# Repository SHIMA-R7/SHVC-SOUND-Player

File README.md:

# SHVC-SOUND スタンドアロンプレイヤー

## ESP32 r0.4基板を使う場合

PCからSPCファイルを再生するESP32用ファームは
`SHVC-SOUND_python/esp32_spc_uploader/`。
準備・書き込み・IPL診断・テスト音の順序は
[ESP32 SPC立ち上げ手順](docs/esp32-spc-bringup.md)を参照。
2026-10-04にSPC全体転送3回連続成功、タイトル曲とWAV由来の短い音声の可聴再生を確認。
WAV一括再生は`SHVC-SOUND_python/tools/wav_clip_esp32.py`を使用する。
[実機確認結果・WAVの使い方・アンプのバイパス](docs/esp32-playback-results.md)も参照。
PCを使わず電源投入から再生する場合は、[単体再生ファーム](docs/esp32-standalone.md)を使用する。
BluetoothでSPC・MIDI・短いWAVを保存・再生し、MIDI演奏や音量・パン・音色を操作する場合は、
[Bluetooth PlayerとWindows操作画面](docs/esp32-bluetooth.md)を使用する。
既存の`esp32_ble_midi/`はBLE／USB MIDI演奏用の別ファーム。
以下のArduino配線と自己診断スケッチはUno／Nano用。

Arduino Uno R3 / Nano (ATmega328P・5Vロジック) で SHVC-SOUND(スーファミ音源モジュール: S-SMP + S-DSP + ARAM + DAC)を駆動し、
`.spc` ファイルを実チップで再生するプロジェクト。音声は TDA7053A(ステレオBTL)で増幅し3.5mmジャックへ出力する。

## 構成

| ディレクトリ | 内容 |
|---|---|
| `SHVC-SOUND-KiCad_project/` | 基板設計(KiCad)。スキーマ・PCB・カスタムフットプリント |
| `SHVC-SOUND_python/` | 再生ソフト一式 |
| `SHVC-SOUND_python/spc_gui.py` | **GUIアプリ**(Tkinter製)。プレイリスト再生・音量調整・ROM解析 |
| `SHVC-SOUND_python/spc_play.py` | PC側。`.spc` を解析しシリアル経由でArduinoへ転送する(CLI/GUI共用) |
| `SHVC-SOUND_python/rom_tools.py` | スーファミROMの内部ヘッダ解析(マッパ判別・チェックサム検証) |
| `SHVC-SOUND_python/spc_uploader/` | Arduino側。シリアルコマンドをSPC700 IPL ROMプロトコルへ変換する |
| `SHVC-SOUND_python/hw_selftest/` | Arduino単体で動く自己診断。PCなしでノイズを鳴らして配線を検証する |
| `docs/minimal-bringup.md` | 最小構成での実機立ち上げ手順と配線表 |

## まず実機で音を確認する

いきなり `spc_play.py` を試す前に、アンプと12V系を外した最小構成で
`hw_selftest/hw_selftest.ino` を走らせる。ハードの問題か転送ソフトの問題かが一発で切り分けられる。
手順と配線表は [docs/minimal-bringup.md](docs/minimal-bringup.md) を参照。

## GUIアプリ

```bash
python spc_gui.py
```

- プレイリストに `.spc` をまとめて登録して再生。ID666タグ(曲名・ゲーム・作曲者)を表示
- DSP音量倍率とアンプPWM音量をスライダーで調整
- 転送はワーカースレッドで実行され、進捗バーとログをリアルタイム表示。中止も可能
- **フォルダ監視**: エミュレータのSPC出力先を指定しておくと、新しくダンプされた
  `.spc` を自動でプレイリストに追加する
- ROM解析タブ: 吸い出したROMのタイトル・マッパ(LoROM/HiROM/ExHiROM)・容量・
  リージョン・チェックサムを表示

### ROMからのSPC抽出について

**ROMの中に `.spc` は入っていない**ため、直接抽出はできない。
`.spc` はSPC700が曲を再生中の ARAM 64KB + DSPレジスタ + CPUレジスタの
スナップショットであり、ROMにあるのはサウンドドライバ・BRRサンプル・
シーケンスデータがバラバラに格納されたもの。ARAMの完成イメージは
ゲームを実際に起動して初めて組み上がる。

実用的な手順は、SPCダンプ機能を持つエミュレータ(Mesen2、bsnes/higan、
一部のSnes9xビルド)でROMを動かし、曲の再生中にダンプすること。
出力先をGUIの「フォルダを監視」に指定しておけば、ダンプした瞬間に
プレイリストへ入って実機で鳴らせる。

## CLIでの使い方

Arduino IDE で `spc_uploader/spc_uploader.ino` を書き込み、以下を実行する。

```bash
python spc_play.py COM3 song.spc
```

`pyserial` が必要:

```bash
pip install pyserial
```

診断用フラグ: `--test`(強制ノイズ再生)、`--skip-bulk`、`--low-addr`、`--only-stub`

## 配線 (Arduino ⇔ SHVC-SOUND 24pin)

| Arduino | SHVC-SOUND pin | 信号 |
|---|---|---|
| D2-D9 | 7-14 | D0-D7 |
| A0 | 3 | A0 |
| A1 | 4 | A1 |
| A2 | 5 | /WR |
| A3 | 6 | /RD |
| A4 | 15 | /RESET |
| D10 | 20 | /MUTE(常時HIGH固定) |
| - | 2 / 1 | CS→+5V / /CS→GND 直結 |
| - | 18, 24 | VCC, VS → +5V |
| - | 19, 23 | GND |
| - | 21, 22 | Audio-L / Audio-R → アンプ入力 |

ロジック系(5V)とアンプ系(12V)は別電源。Arduinoのレギュレータからアンプ用12Vを取らないこと。

## 既知の問題

- **復元スタブが曲データを上書きする**: `spc_play.py` のDSP復元スタブは約800バイトあり `$FFC0` 直下(≒`$FC9B`)に配置されるが、
  この領域はメインRAM転送範囲(`$0100-$FFBF`)と重なるため曲データを約800バイト破壊する。
  この領域をサンプルやエコーバッファに使う曲ではノイズが出る。エコーバッファ領域への配置か、スタブのループ化による小型化が要検討。
- **基板のDRC違反が未修正**: シルク重なり2件、シルクが銅箔にかかる6件、フットプリント型不一致1件、ライブラリ不一致1件。
- 実機での動作確認は未完了。
- **基板のSHVC-SOUNDフットプリントに1番ピンの表示が無い**: `SHVC-SOUND-MB.kicad_mod` は
  パッド24個すべてが丸、シルクにピン番号も1番マーカーも無い(リファレンス指定子のみ)。
  コネクタ自体にキーが無く逆挿しできてしまうため、シルクに `1` の印字と極性マークを追加すべき。
- **基板はArduino Nanoフットプリント**(`Module:Arduino_Nano_WithMountingHoles`)。
  Uno R3はピン互換だがフットプリントが合わないため、基板に載せる場合は要変更。ジャンパ配線での検証には支障なし。

## ライセンス / 帰属

基板設計の一部は [OpenSFC](https://github.com/starlightk7/OpenSFC)(© 2025 starlightk7、CERN-OHL-S)に由来する。
詳細と再頒布時の義務は `SHVC-SOUND-KiCad_project/SHVC-SOUND-KiCad/THIRD_PARTY_NOTICE_OpenSFC.txt` を参照。
公開・頒布する場合は CERN-OHL-S 3.3 に従い、改変内容の要約を同NOTICEに追記すること。

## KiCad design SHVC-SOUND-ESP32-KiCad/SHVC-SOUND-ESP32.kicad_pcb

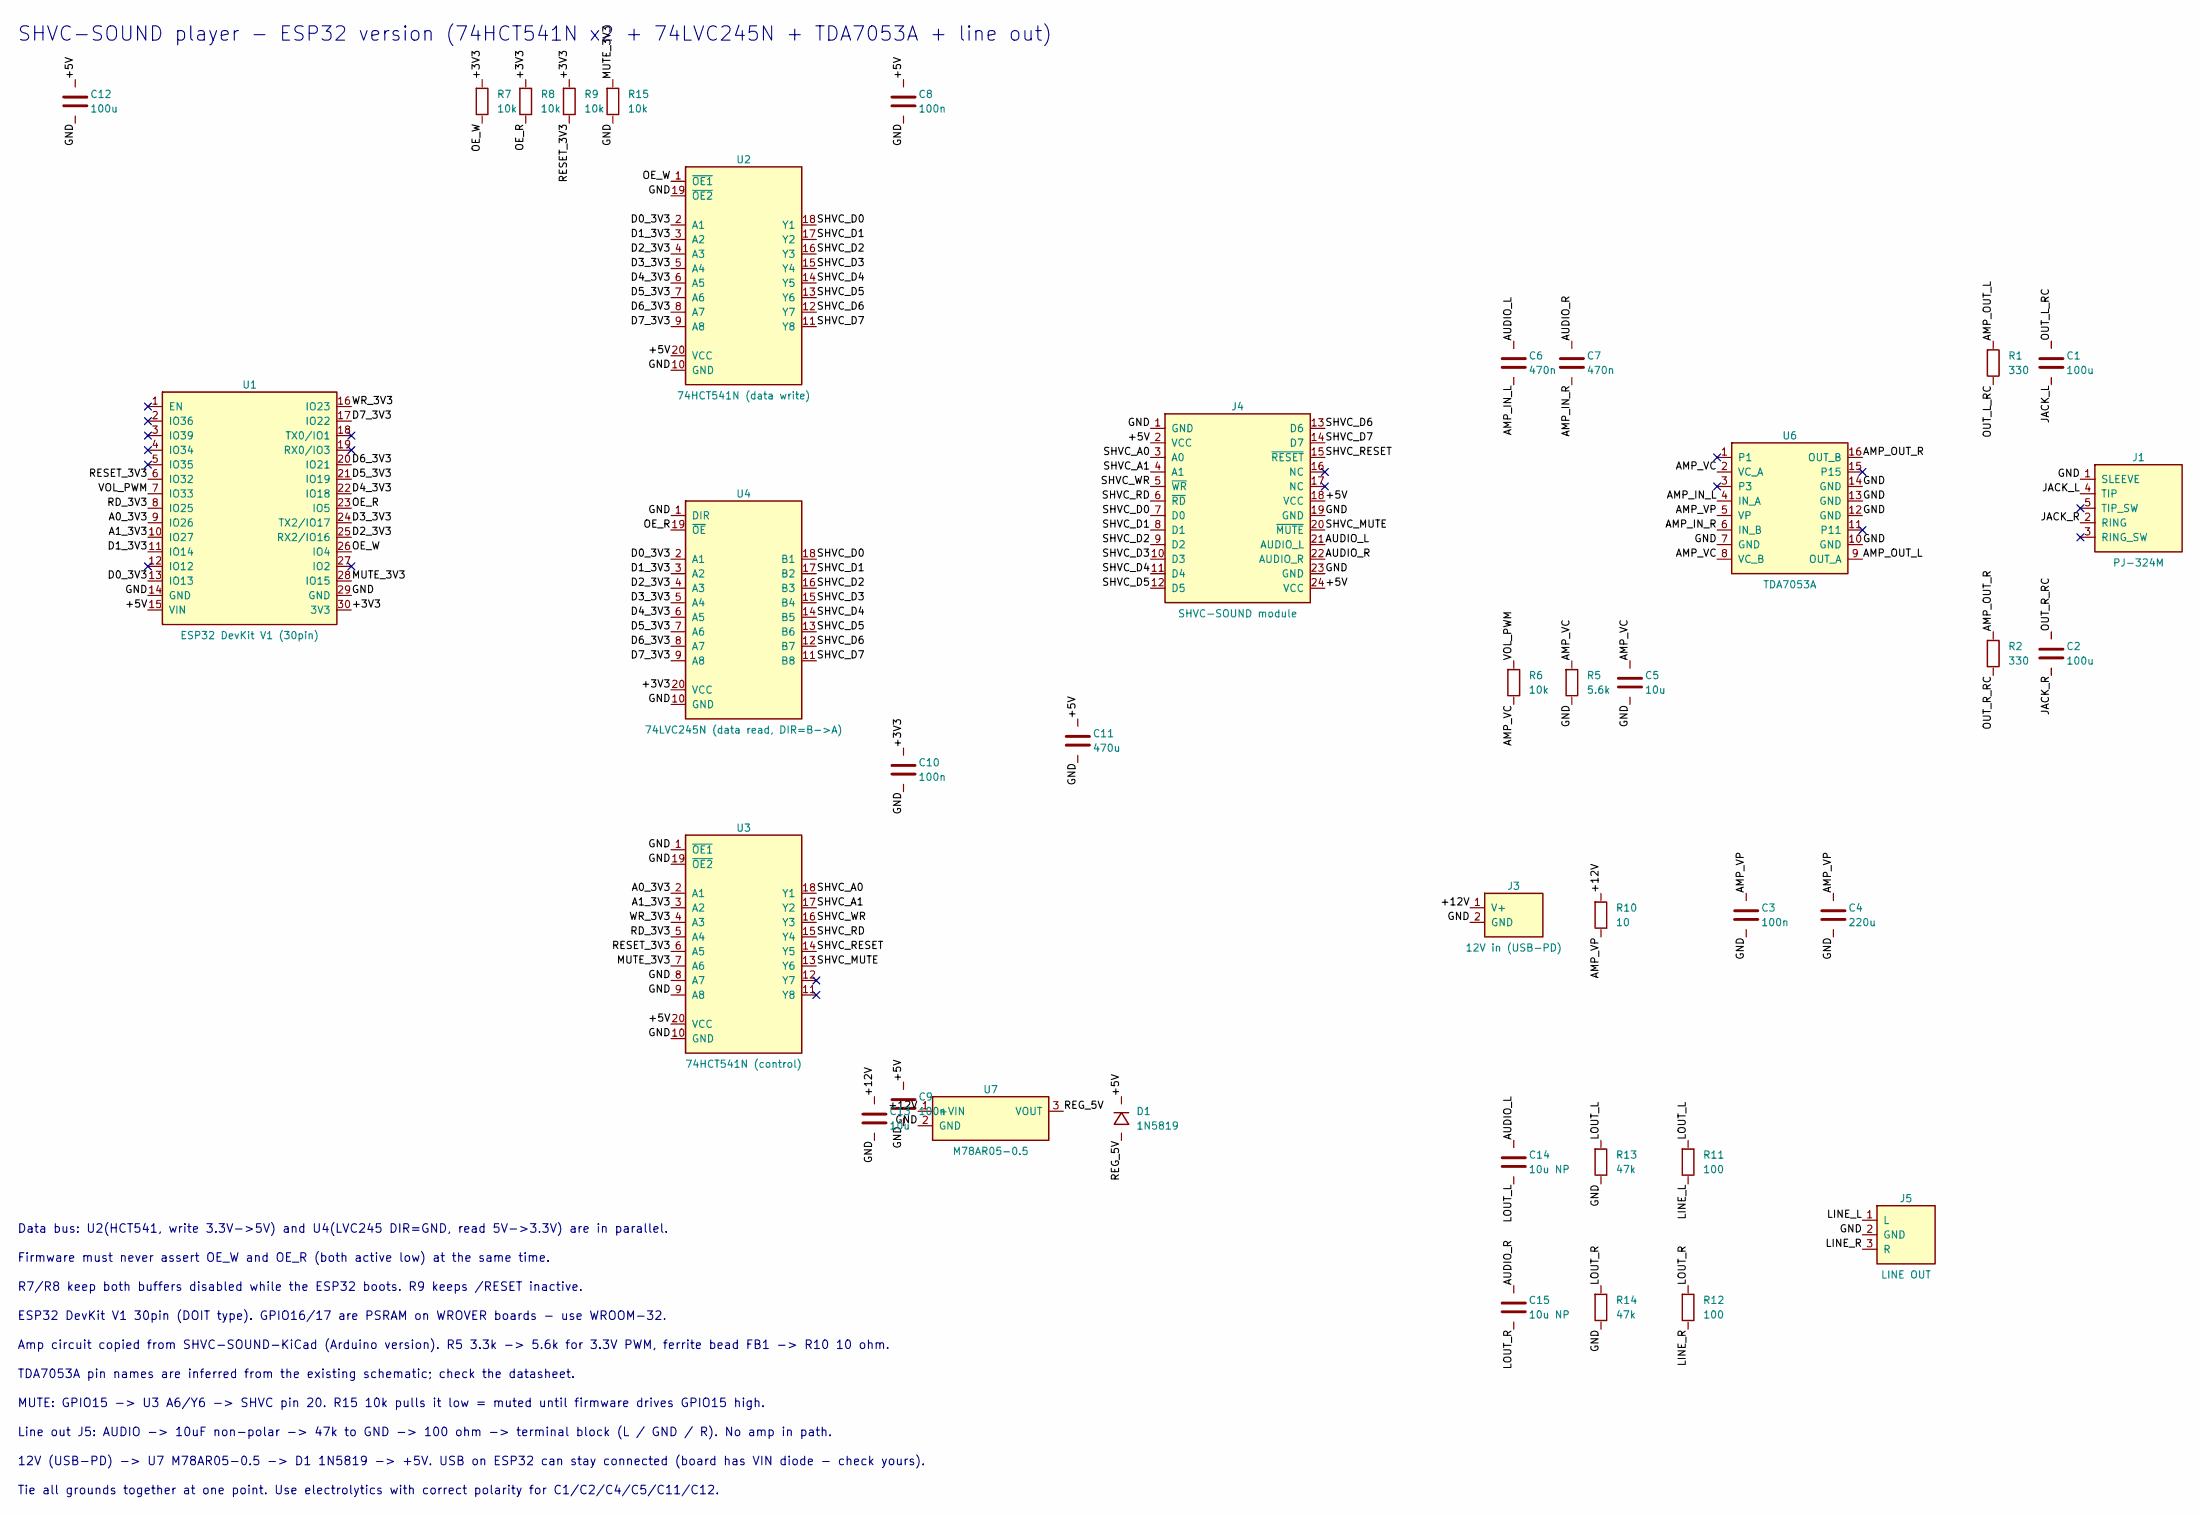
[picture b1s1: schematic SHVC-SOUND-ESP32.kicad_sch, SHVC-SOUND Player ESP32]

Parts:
C1, C2, C12: 100u; CP_Radial_D6.3mm_P2.50mm
C3, C8, C9, C10: 100n; C_Disc_D3.0mm_W1.6mm_P2.50mm
C4: 220u; CP_Radial_D8.0mm_P3.50mm
C5, C13: 10u; CP_Radial_D5.0mm_P2.00mm
C6, C7: 470n; C_Disc_D5.0mm_W2.5mm_P5.00mm
C11: 470u; CP_Radial_D10.0mm_P5.00mm
C14, C15: 10u NP; CP_Radial_D4.0mm_P1.50mm
D1: 1N5819; D_DO-41_SOD81_P7.62mm_Horizontal
J1: PJ-324M
J3: 12V in (USB-PD); PD_INPUT_MODULE_2P
J4: SHVC-SOUND module; SHVC-SOUND-MB
J5: LINE OUT; TerminalBlock_Phoenix_PT-1,5-3-3.5-H_1x03_P3.50mm_Horizontal
R1, R2: 330; R_Axial_DIN0207_L6.3mm_D2.5mm_P7.62mm_Horizontal
R5: 5.6k; R_Axial_DIN0207_L6.3mm_D2.5mm_P7.62mm_Horizontal
R6, R7, R8, R9: 10k; R_Axial_DIN0207_L6.3mm_D2.5mm_P7.62mm_Horizontal
R10: 10; R_Axial_DIN0207_L6.3mm_D2.5mm_P7.62mm_Horizontal
R11, R12: 100; R_Axial_DIN0207_L6.3mm_D2.5mm_P2.54mm_Vertical
R13, R14: 47k; R_Axial_DIN0207_L6.3mm_D2.5mm_P2.54mm_Vertical
R15: 10k; R_Axial_DIN0207_L6.3mm_D2.5mm_P2.54mm_Vertical
U1: ESP32 DevKit V1 (30pin); ESP32-DevKit-30_Socket
U2: 74HCT541N (data write); DIP-20_W7.62mm
U3: 74HCT541N (control); DIP-20_W7.62mm
U4: 74LVC245N (data read, DIR=B->A); DIP-20_W7.62mm
U6: TDA7053A; DIP-16_W7.62mm
U7: M78AR05-0.5; DCDC_SIP3_7805

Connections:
+3V3: C10.1 (K), R7.1 (K), R8.1 (K), R9.1 (K), U1.30 (3V3), U4.20 (VCC)
+5V: C8.1 (K), C9.1 (K), C11.1 (K), C12.1 (K), D1.1 (K), J4.2 (VCC), J4.18 (VCC), J4.24 (VCC), U1.15 (VIN), U2.20 (VCC), U3.20 (VCC)
+12V: C13.1 (K), J3.1 (V+), R10.1 (K), U7.1 (+VIN)
A0_3V3: U1.9 (IO26), U3.2 (A1)
A1_3V3: U1.10 (IO27), U3.3 (A2)
AMP_IN_L: C6.2 (A), U6.4 (IN_A)
AMP_IN_R: C7.2 (A), U6.6 (IN_B)
AMP_OUT_L: R1.1 (K), U6.9 (OUT_A)
AMP_OUT_R: R2.1 (K), U6.16 (OUT_B)
AMP_VC: C5.1 (K), R5.1 (K), R6.2 (A), U6.2 (VC_A), U6.8 (VC_B)
AMP_VP: C3.1 (K), C4.1 (K), R10.2 (A), U6.5 (VP)
AUDIO_L: C6.1 (K), C14.1 (K), J4.21 (AUDIO_L)
AUDIO_R: C7.1 (K), C15.1 (K), J4.22 (AUDIO_R)
D0_3V3: U1.13 (IO13), U2.2 (A1), U4.2 (A1)
D1_3V3: U1.11 (IO14), U2.3 (A2), U4.3 (A2)
D2_3V3: U1.25 (RX2/IO16), U2.4 (A3), U4.4 (A3)
D3_3V3: U1.24 (TX2/IO17), U2.5 (A4), U4.5 (A4)
D4_3V3: U1.22 (IO18), U2.6 (A5), U4.6 (A5)
D5_3V3: U1.21 (IO19), U2.7 (A6), U4.7 (A6)
D6_3V3: U1.20 (IO21), U2.8 (A7), U4.8 (A7)
D7_3V3: U1.17 (IO22), U2.9 (A8), U4.9 (A8)
GND: C3.2 (A), C4.2 (A), C5.2 (A), C8.2 (A), C9.2 (A), C10.2 (A), C11.2 (A), C12.2 (A), C13.2 (A), J1.1 (SLEEVE), J3.2 (GND), J4.1 (GND), J4.19 (GND), J4.23 (GND), J5.2 (GND), R5.2 (A), R13.2 (A), R14.2 (A), R15.2 (A), U1.14 (GND), U1.29 (GND), U2.10 (GND), U2.19 (~OE2), U3.1 (~OE1), U3.8 (A7), U3.9 (A8), U3.10 (GND), U3.19 (~OE2), U4.1 (DIR), U4.10 (GND), U6.7 (GND), U6.10 (GND), U6.12 (GND), U6.13 (GND), U6.14 (GND), U7.2 (GND)
JACK_L: C1.2 (A), J1.4 (TIP)
JACK_R: C2.2 (A), J1.2 (RING)
LINE_L: J5.1 (L), R11.2 (A)
LINE_R: J5.3 (R), R12.2 (A)
LOUT_L: C14.2 (A), R11.1 (K), R13.1 (K)
LOUT_R: C15.2 (A), R12.1 (K), R14.1 (K)
MUTE_3V3: R15.1 (K), U1.28 (IO15), U3.7 (A6)
OE_R: R8.2 (A), U1.23 (IO5), U4.19 (~OE)
OE_W: R7.2 (A), U1.26 (IO4), U2.1 (~OE1)
OUT_L_RC: C1.1 (K), R1.2 (A)
OUT_R_RC: C2.1 (K), R2.2 (A)
RD_3V3: U1.8 (IO25), U3.5 (A4)
REG_5V: D1.2 (A), U7.3 (VOUT)
RESET_3V3: R9.2 (A), U1.6 (IO32), U3.6 (A5)
SHVC_A0: J4.3 (A0), U3.18 (Y1)
SHVC_A1: J4.4 (A1), U3.17 (Y2)
SHVC_D0: J4.7 (D0), U2.18 (Y1), U4.18 (B1)
SHVC_D1: J4.8 (D1), U2.17 (Y2), U4.17 (B2)
SHVC_D2: J4.9 (D2), U2.16 (Y3), U4.16 (B3)
SHVC_D3: J4.10 (D3), U2.15 (Y4), U4.15 (B4)
SHVC_D4: J4.11 (D4), U2.14 (Y5), U4.14 (B5)
SHVC_D5: J4.12 (D5), U2.13 (Y6), U4.13 (B6)
SHVC_D6: J4.13 (D6), U2.12 (Y7), U4.12 (B7)
SHVC_D7: J4.14 (D7), U2.11 (Y8), U4.11 (B8)
SHVC_MUTE: J4.20 (~MUTE), U3.13 (Y6)
SHVC_RD: J4.6 (~RD), U3.15 (Y4)
SHVC_RESET: J4.15 (~RESET), U3.14 (Y5)
SHVC_WR: J4.5 (~WR), U3.16 (Y3)
VOL_PWM: R6.1 (K), U1.7 (IO33)
WR_3V3: U1.16 (IO23), U3.4 (A3)

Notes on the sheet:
SHVC-SOUND player - ESP32 version (74HCT541N x2 + 74LVC245N + TDA7053A + line out)
Data bus: U2(HCT541, write 3.3V->5V) and U4(LVC245 DIR=GND, read 5V->3.3V) are in parallel.
Firmware must never assert OE_W and OE_R (both active low) at the same time.
R7/R8 keep both buffers disabled while the ESP32 boots. R9 keeps /RESET inactive.
ESP32 DevKit V1 30pin (DOIT type). GPIO16/17 are PSRAM on WROVER boards - use WROOM-32.
Amp circuit copied from SHVC-SOUND-KiCad (Arduino version). R5 3.3k -> 5.6k for 3.3V PWM, ferrite bead FB1 -> R10 10 ohm.
TDA7053A pin names are inferred from the existing schematic; check the datasheet.
MUTE: GPIO15 -> U3 A6/Y6 -> SHVC pin 20. R15 10k pulls it low = muted until firmware drives GPIO15 high.
Line out J5: AUDIO -> 10uF non-polar -> 47k to GND -> 100 ohm -> terminal block (L / GND / R). No amp in path.
12V (USB-PD) -> U7 M78AR05-0.5 -> D1 1N5819 -> +5V. USB on ESP32 can stay connected (board has VIN diode - check yours).
Tie all grounds together at one point. Use electrolytics with correct polarity for C1/C2/C4/C5/C11/C12.

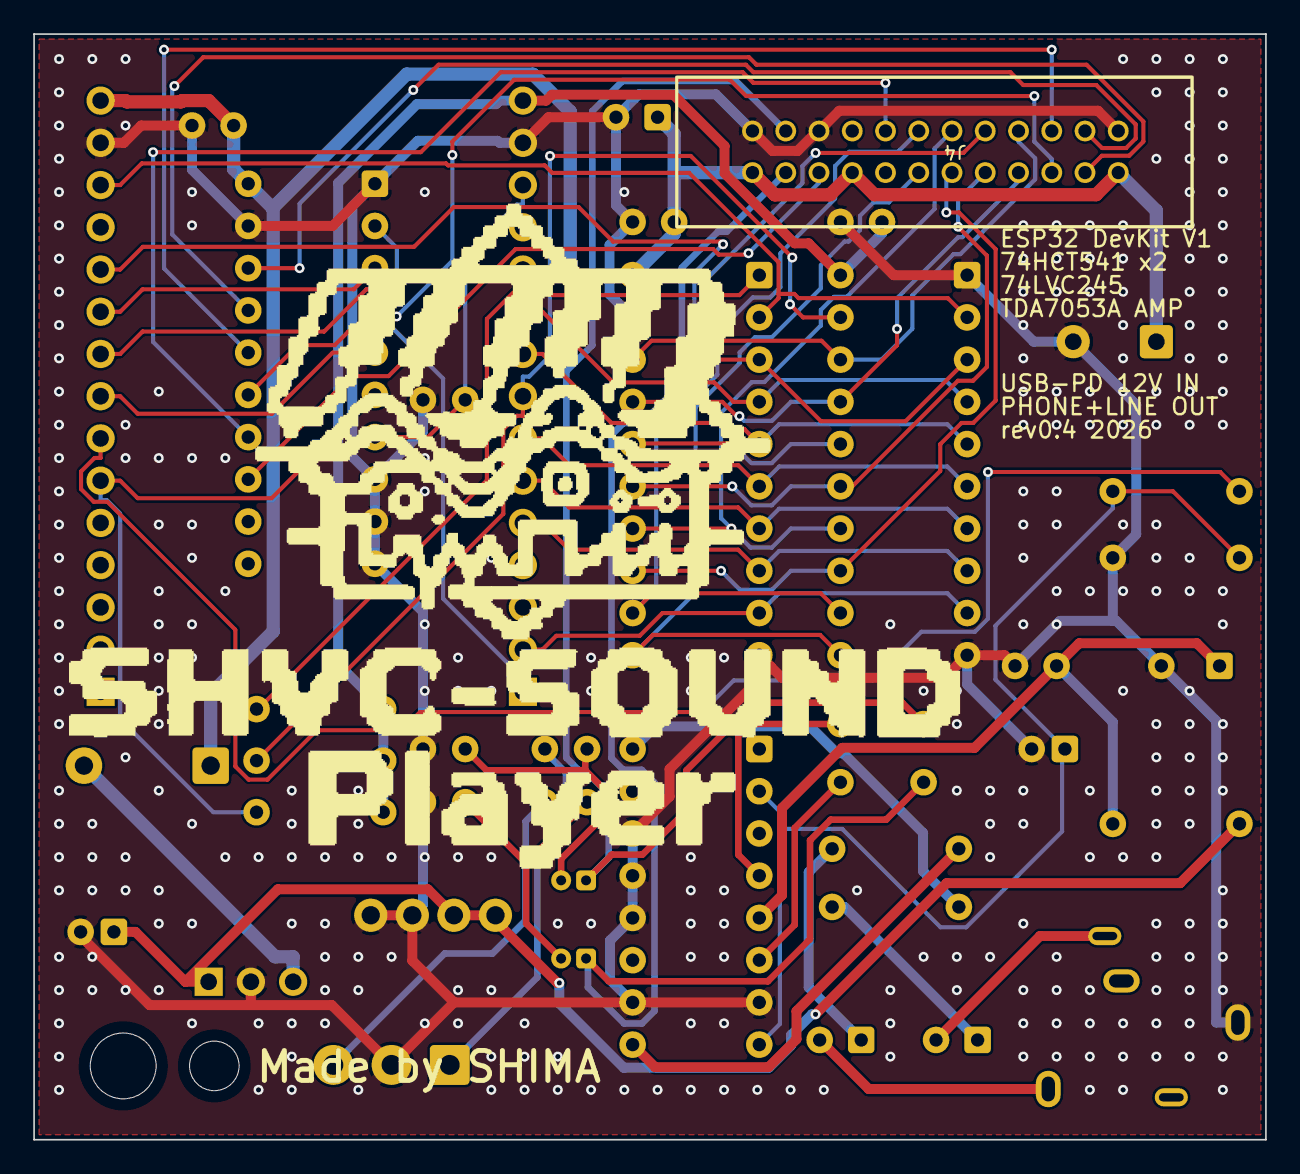
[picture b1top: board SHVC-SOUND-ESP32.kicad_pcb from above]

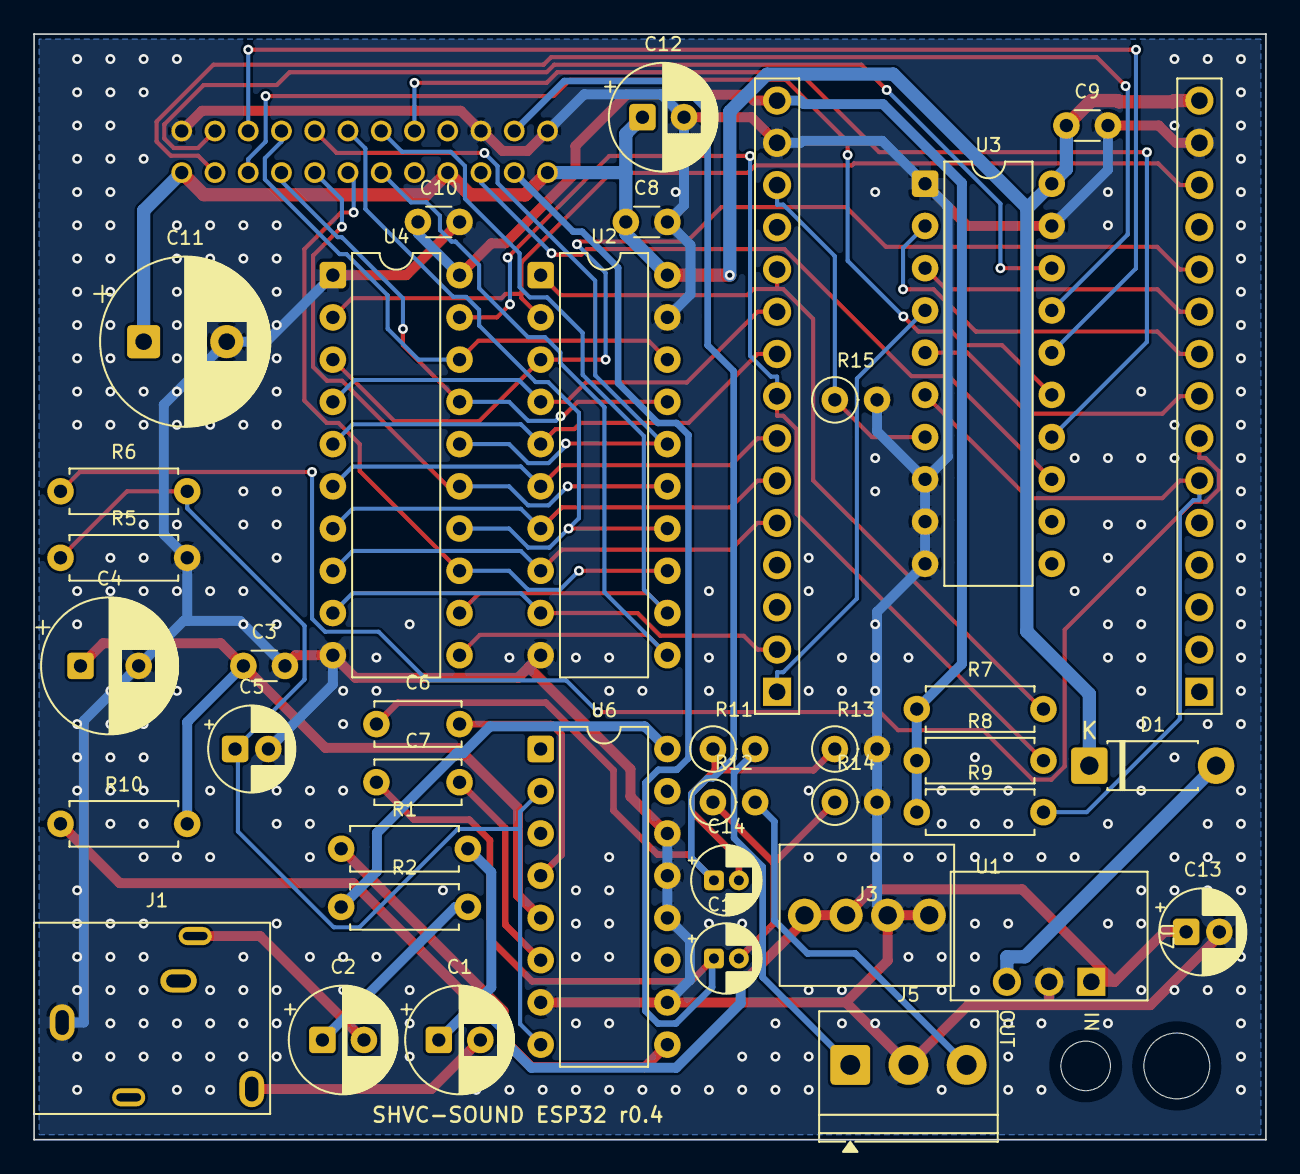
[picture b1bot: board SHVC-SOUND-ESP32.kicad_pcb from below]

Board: 2 copper layers, 74.1 x 66.5 mm, 41 parts (38 on the bottom side), 52 nets.

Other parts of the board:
H1: hole 3.96mm; NPTH_Hole_3.96mm
H2: hole 2.98mm; NPTH_Hole_2.98mm

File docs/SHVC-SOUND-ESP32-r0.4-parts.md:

# SHVC-SOUND-ESP32 rev0.4 部品表

対象：ESP32版 rev0.4（74.09 × 66.5mm）。2026-10-02時点。現行BOMから自動生成し、PCBの部品番号を照合。**実機動作は未検証**。

Arduino Nano版の部品表ではありません。SHVC-SOUND音源モジュール本体、12V対応USB-PD電源・ケーブルは別途用意してください。

## 1. IC・モジュール・電源

| 部品番号 | 数量 | 品名・値 | 仕様・取り付け上の注意 |
| --- | --- | --- | --- |
| U2 | 1 | 74HCT541N | DIP-20。データ書き込み(3.3V→5V)。ICソケット可 |
| U3 | 1 | 74HCT541N | DIP-20。制御線(3.3V→5V)。ESP32の下なのでソケット不可・直付け |
| U4 | 1 | 74LVC245N | DIP-20。データ読み出し(5V→3.3V)。ICソケット可 |
| U6 | 1 | TDA7053A | DIP-16。ステレオアンプ。ICソケット可 |
| U1 | 1 | ESP32 DevKit V1 | 30ピン(DOIT互換) 列間25.4mm。WROOM-32搭載品 |
| J3 | 1 | USB-PDトリガーモジュール(12V) | 既存基板と同じPD_INPUT_MODULE。全体の電源入力(12V) |
| U7 | 1 | M78AR05-0.5(MINMAX) | 12V→5V 0.5A DC-DCコンバータ 7805互換SIP3。既存Arduino版と同じ部品 |
| D1 | 1 | 1N5819 | ショットキーダイオード 1A DO-41 リード間7.62mm。DC-DC出力→+5V(USB給電との逆流防止) |

## 2. 抵抗

| 部品番号 | 数量 | 品名・値 | 仕様・取り付け上の注意 |
| --- | --- | --- | --- |
| R1 R2 | 2 | 330Ω | 1/4W 炭素皮膜 リード間7.62mm。ヘッドホン出力直列 |
| R5 | 1 | 5.6kΩ | 1/4W 炭素皮膜 リード間7.62mm。音量電圧の分圧(3.3V PWM用) |
| R10 | 1 | 10Ω | 1/4W 炭素皮膜 リード間7.62mm。12V入力のノイズ除去(C4と約72Hzのローパス) |
| R6 R7 R8 R9 | 4 | 10kΩ | 1/4W 炭素皮膜 リード間7.62mm。R6=音量PWM R7/R8=OEプルアップ R9=/RESETプルアップ |
| R11 R12 | 2 | 100Ω | 1/4W 炭素皮膜 立て付け(リード間2.54mm)。ライン出力の保護(ESP32の下なので高さ10mm以下に) |
| R13 R14 | 2 | 47kΩ | 1/4W 炭素皮膜 立て付け(リード間2.54mm)。ライン出力を0V基準に固定(抜き差し時のポップ防止) |
| R15 | 1 | 10kΩ | 1/4W 炭素皮膜 立て付け(リード間2.54mm)。MUTE引き下げ(ESP32起動中は消音) |

## 3. コンデンサ

| 部品番号 | 数量 | 品名・値 | 仕様・取り付け上の注意 |
| --- | --- | --- | --- |
| C3 C8 C9 C10 | 4 | 100nF | 積層セラミック 50V リード間2.5mm。パスコン |
| C6 C7 | 2 | 470nF | 積層セラミックまたはフィルム 50V リード間5.0mm。音声入力の直流カット |
| C5 | 1 | 10µF | 電解 16V以上 φ5mm リード間2.0mm。音量電圧の平滑 |
| C13 | 1 | 10µF | 電解 25V以上 φ5mm リード間2.0mm。DC-DC入力(12V) |
| C14 C15 | 2 | 10µF 無極性(バイポーラ) | 電解 16V以上 φ4mm リード間1.5mm。ライン出力の直流カット(向きなし) |
| C1 C2 | 2 | 100µF | 電解 16V以上 φ6.3mm リード間2.5mm。ヘッドホン出力の直流カット |
| C12 | 1 | 100µF | 電解 10V以上 φ6.3mm リード間2.5mm。ESP32側5V |
| C4 | 1 | 220µF | 電解 25V以上 φ8mm リード間3.5mm。12V平滑 |
| C11 | 1 | 470µF | 電解 10V以上 φ10mm リード間5.0mm。SHVC-SOUND側5V |

## 4. コネクタ・ソケット・基板

| 部品番号 | 数量 | 品名・値 | 仕様・取り付け上の注意 |
| --- | --- | --- | --- |
| J1 | 1 | PJ-324M | 3.5mmステレオジャック 5ピン(SOFNG LCSC C22355739)。1=GND 4=L 2=R(推定・要導通確認) |
| J5 | 1 | ターミナルブロック 3P | 3.5mmピッチ 横入れ(Phoenix PT-1.5-3-3.5-H 相当)。ライン出力 L/GND/R(アンプを通さない) |
| J4用 | 2 | ピンソケット 1x12 | 2.0mmピッチ 1列 12ピン。2本を列間2.5mmで並べてSHVC-SOUNDを受ける |
| U1用 | 2 | ピンソケット 1x15 | 2.54mmピッチ 1列 15ピン 高さ8.5mm前後。ESP32を挿す |
| - | 1 | SHVC-SOUND-ESP32 r0.4 | 2層 74.09×66.5mm 板厚1.6mm |

## 5. 任意のソケット・固定部品

| 部品番号 | 数量 | 品名・値 | 仕様・取り付け上の注意 |
| --- | --- | --- | --- |
| U2 U4用 | 2 | ICソケット 20ピン | DIP-20 300mil |
| U6用 | 1 | ICソケット 16ピン | DIP-16 300mil |
| H1 H2 | 各1 | スペーサー・ネジ | M3(穴径約4.0mm)とM2.5(穴径約3.0mm)。SHVC-SOUNDとの固定用 |

## 6. 今回の代替部品と取り付けの注意

以下は標準BOMとは別の代替メモです。標準の指定値は上の表に残しています。

| 対象 | 今回の扱い |
| --- | --- |
| R7・R8・R9 | 3kΩへの代替可。3.3Vへのプルアップで、LOW時は約1.1mA。10kΩと混在しても可。R6の音量分圧抵抗とは区別する。 |
| D1 | 標準は1N5819。1N4002は逆流防止として働くが電圧降下が増えるため、代替動作は未検証。採用する場合はUSBを外して基板電源だけで、D1通過後の電圧を確認する。 |
| U3 | ESP32の下に入るためICソケットを使わず直付け。 |
| R11～R15・C14/C15 | rev0.4に含まれる部品。R11～R15は立て付け。R11/R12はESP32の下なので高さ10mm以下。C14/C15は無極性。 |
| J1 | ジャックの端子対応は未検証。使用する現物で導通を確認し、一致しない場合は配線を現物に合わせる。 |

## 7. 確認状況・元データ

| 項目 | 確認状況 |
| --- | --- |
| 基板版数 | PCB内のrev0.4表記を確認 |
| 部品番号 | PCBの全41個の部品番号がBOMに含まれることを照合 |
| 部品の値・仕様 | 現行BOMから自動転記。抵抗・コンデンサ・IC・電源のPCB値を生成時に出力し照合 |
| 実機動作・代替ダイオード | 未検証。組み立て後に電源電圧・通信・発音を順番に確認 |

- 元BOM：`SHVC-SOUND-ESP32-BOM.csv`（SHVC-SOUND直下）
- 基板：`SHVC-SOUND-Player/SHVC-SOUND-ESP32-KiCad/SHVC-SOUND-ESP32.kicad_pcb`
- この部品表：`SHVC-SOUND-Player/docs/SHVC-SOUND-ESP32-r0.4-parts.md`
- 生成スクリプト：`SHVC-SOUND-Player/docs/build_rev04_parts.py`
